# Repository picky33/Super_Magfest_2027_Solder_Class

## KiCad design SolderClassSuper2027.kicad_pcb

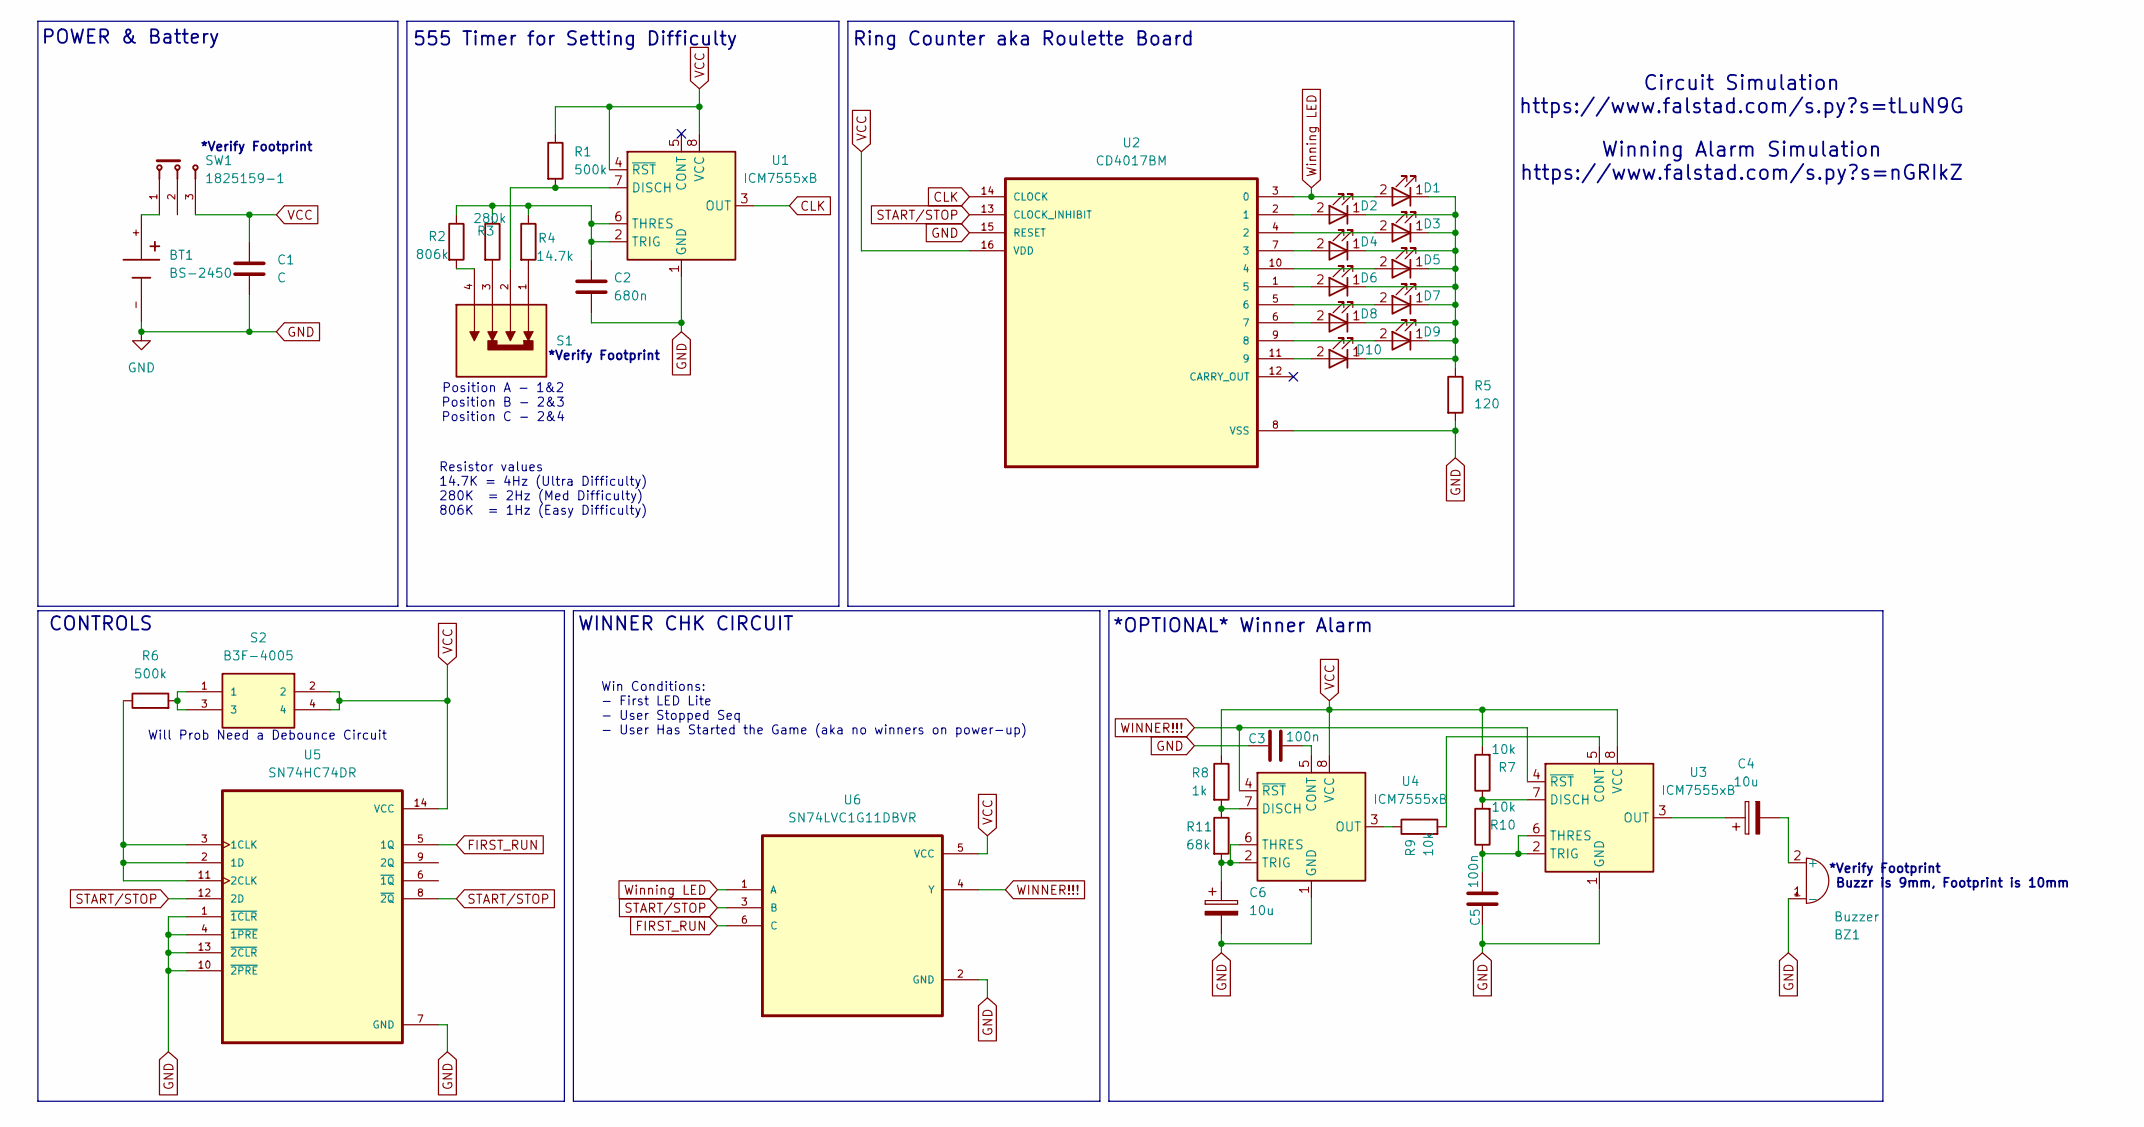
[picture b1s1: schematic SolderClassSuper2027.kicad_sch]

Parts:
BT1: BS-2450; BAT_BS-2450
BZ1: Buzzer; Buzzer_D14mm_H7mm_P10mm; Digikey 433-1285-ND
C1: C; C_Axial_L3.8mm_D2.6mm_P12.50mm_Horizontal
C2: 680n; C_Disc_D10.5mm_W5.0mm_P10.00mm
C3, C5: 100n; C_Disc_D10.5mm_W5.0mm_P10.00mm
C4, C6: 10u; CP_Radial_Tantal_D5.5mm_P5.00mm
D1: LED; LED_D4.0mm
D2, D3, D4, D5, D6, D7, D8, D9, D10: LED; LED_0805_2012Metric_Pad1.15x1.40mm_HandSolder
R1, R6: 500k; R_Axial_DIN0309_L9.0mm_D3.2mm_P15.24mm_Horizontal
R2: 806k; R_Axial_DIN0309_L9.0mm_D3.2mm_P15.24mm_Horizontal
R3: 280k; R_Axial_DIN0309_L9.0mm_D3.2mm_P15.24mm_Horizontal
R4: 14.7k; R_Axial_DIN0309_L9.0mm_D3.2mm_P15.24mm_Horizontal
R5: 120; R_0805_2012Metric_Pad1.20x1.40mm_HandSolder
R7, R9, R10: 10k; R_Axial_DIN0309_L9.0mm_D3.2mm_P15.24mm_Horizontal
R8: 1k; R_Axial_DIN0309_L9.0mm_D3.2mm_P15.24mm_Horizontal
R11: 68k; R_Axial_DIN0309_L9.0mm_D3.2mm_P15.24mm_Horizontal
S1: SLW-178562-3A-S-D; SW_SLW-SK13D07VG5; PARTREV 1.01
S2: B3F-4005; B3F-4055; Mouser_Part_Number 653-B3F-4005
SW1: 1825159-1; SW_1825159-1; MPN 1825159-1
U1, U3, U4: ICM7555xB; SOIC-8_3.9x4.9mm_P1.27mm
U2: CD4017BM; SOIC127P600X175-16N
U5: SN74HC74DR; SOIC127P600X175-14N
U6: SN74LVC1G11DBVR; SOT95P280X145-6N

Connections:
CLK: U1.3 (OUT), U2.14 (CLOCK)
FIRST_RUN: U5.5 (1Q), U6.6 (C)
GND: BT1.-, BZ1.1 (-), C1.2, C2.2, C3.1, C5.1, C6.2, R5.2, U1.1 (GND), U2.8 (VSS), U2.15 (RESET), U3.1 (GND), U4.1 (GND), U5.1 (~1CLR), U5.4 (~1PRE), U5.7 (GND), U5.10 (~2PRE), U5.13 (~2CLR), U6.2 (GND)
unnamed: BT1.+, SW1.1
unnamed: BZ1.2 (+), C4.2
unnamed: D1.1, D2.1, D3.1, D4.1, D5.1, D6.1, D7.1, D8.1, D9.1, D10.1, R5.1
unnamed: R2.2, S1.4
unnamed: R3.2, S1.3
unnamed: R4.2, S1.1
unnamed: R6.2, S2.1, S2.3
unnamed: R1.2, S1.2, U1.7 (DISCH)
unnamed: C2.1, R2.1, R3.1, R4.1, U1.2 (TRIG), U1.6 (THRES)
unnamed: D2.2, U2.2 (1)
unnamed: D3.2, U2.4 (2)
unnamed: D4.2, U2.7 (3)
unnamed: D5.2, U2.10 (4)
unnamed: D6.2, U2.1 (5)
unnamed: D7.2, U2.5 (6)
unnamed: D8.2, U2.6 (7)
unnamed: D9.2, U2.9 (8)
unnamed: D10.2, U2.11 (9)
unnamed: R9.2, U3.5 (CONT)
unnamed: R7.1, R10.2, U3.7 (DISCH)
unnamed: C4.1, U3.3 (OUT)
unnamed: C5.2, R10.1, U3.2 (TRIG), U3.6 (THRES)
unnamed: C3.2, U4.5 (CONT)
unnamed: R8.2, R11.1, U4.7 (DISCH)
unnamed: R9.1, U4.3 (OUT)
unnamed: C6.1, R11.2, U4.2 (TRIG), U4.6 (THRES)
unnamed: R6.1, U5.2 (1D), U5.3 (1CLK), U5.11 (2CLK)
VCC: C1.1, R1.1, R7.2, R8.1, S2.2, S2.4, SW1.3, U1.4 (~RST), U1.8 (VCC), U2.16 (VDD), U3.8 (VCC), U4.8 (VCC), U5.14 (VCC), U6.5 (VCC)
WINNER!!!: U3.4 (~RST), U4.4 (~RST), U6.4 (Y)
Winning LED: D1.2, U2.3 (0), U6.1 (A)

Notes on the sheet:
CONTROLS
*Verify Footprint
Resistor values 14.7K = 4Hz (Ultra Difficulty) 280K = 2Hz (Med Difficulty) 806K = 1Hz (Easy Difficulty)
*OPTIONAL* Winner Alarm
Winning Alarm Simulation https://www.falstad.com/s.py?s=nGRIkZ
Position A - 1&2 Position B - 2&3 Position C - 2&4
WINNER CHK CIRCUIT
*Verify Footprint Buzzr is 9mm, Footprint is 10mm
Win Conditions: - First LED Lite - User Stopped Seq - User Has Started the Game (aka no winners on power-up)
POWER & Battery
555 Timer for Setting Difficulty
Ring Counter aka Roulette Board
Circuit Simulation https://www.falstad.com/s.py?s=tLuN9G
Will Prob Need a Debounce Circuit

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
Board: 2 copper layers, 38 parts (0 on the bottom side), 34 nets, no tracks yet.
